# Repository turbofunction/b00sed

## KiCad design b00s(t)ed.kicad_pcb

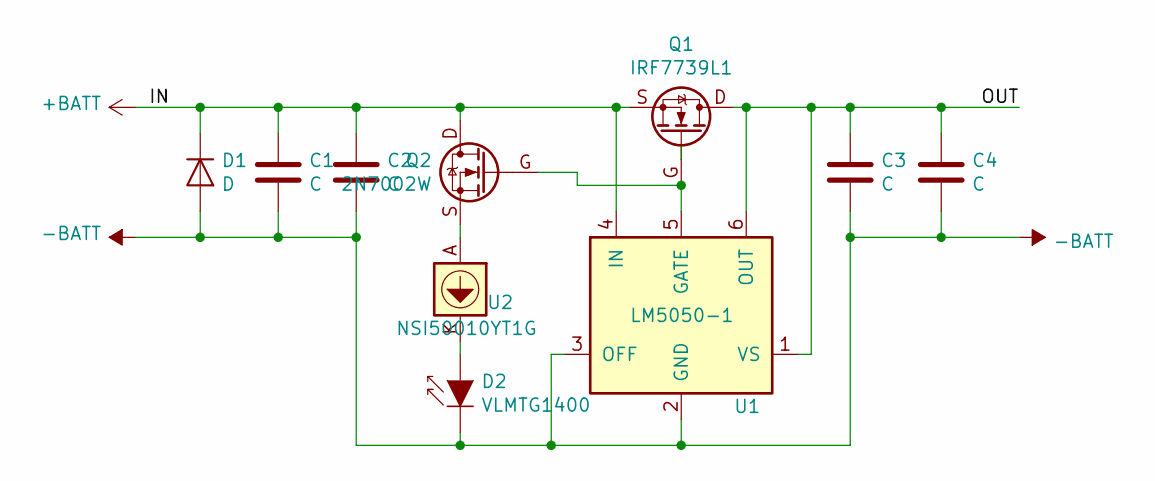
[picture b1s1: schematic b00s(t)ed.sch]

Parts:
C1, C2, C3, C4: C; C_1206_3216Metric
D1: D; D_SMB
D2: VLMTG1400; D_0603_1608Metric
Q1: IRF7739L1; DirectFET_L8
Q2: 2N7002W; SOT-323_SC-70-FET
U1: LM5050-1; SOT-23-6
U2: NSI50010YT1G; SOD-123

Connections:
+BATT: C1.1, C2.1, D1.1 (K), Q1.S, Q2.D, U1.4 (IN)
-BATT: C1.2, C2.2, C3.2, C4.2, D1.2 (A), D2.1 (K), U1.2 (GND), U1.3 (OFF)
/OUT: C3.1, C4.1, Q1.D, U1.1 (VS), U1.6 (OUT)
unnamed: D2.2 (A), U2.K (Cathode)
unnamed: Q1.G, Q2.G, U1.5 (GATE)
unnamed: Q2.S, U2.A (Anode)

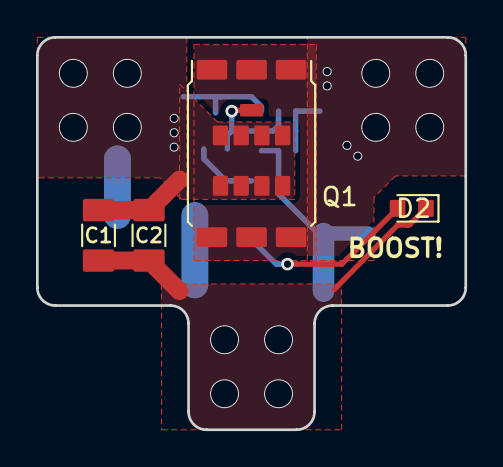
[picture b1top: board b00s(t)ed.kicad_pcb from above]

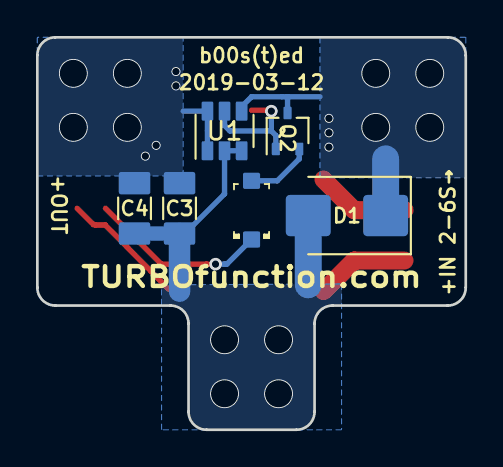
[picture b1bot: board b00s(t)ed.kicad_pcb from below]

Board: 2 copper layers, 23.8 x 21.8 mm, 10 parts (6 on the bottom side), 6 nets.

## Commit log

2019-01-30 Learning KiCad
2019-01-30 Doc said to include
2019-01-31 Fixed connectors
2019-02-01 backup
2019-02-02 First version ready for order
2019-02-04 ordered
2019-02-11 Switch over to LM5050-2
2019-02-11 tidy
2019-02-12 Switch over to LM5050-1
2019-02-12 Date update
2019-02-12 Include gerbers
2019-02-19 Wire tabs update
2019-02-19 7x7mm pads
2019-02-19 2019-02-19
2019-03-12 Fucking kicad has pin mappings wrong
